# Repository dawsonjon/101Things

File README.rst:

.. image:: https://readthedocs.org/projects/chips-20/badge/?version=latest
    :target: https://readthedocs.org/projects/chips-20/badge/?version=latest

101 Things
==========

Welcome to *101 Things*, a collection of projects that celebrate creativity and
hands-on ingenuity.  If you share a passion for making things, you've come to
the right place. Each project uses simple designs, and basic tools, to push the
creative boundaries of a home tinkerer.  Join me on this exploration of
crafting, coding, and constructing, as we unlock the magic of making, one
project at a time.

Documentation
-------------

`ReadTheDocs <https://101-things.readthedocs.io/en/latest/>`_.

Projects so far
---------------

Pi Pico Rx - A crystal radio for the digital age?
"""""""""""""""""""""""""""""""""""""""""""""""""

.. image:: docs/images/thumbnail5.png
  :target: https://github.com/dawsonjon/PicoRX/assets/717535/4846c78d-21c3-42e8-bcdf-278cc2bdadcb

DIY Multi-Effect Guitar Unit
""""""""""""""""""""""""""""

.. image:: docs/images/headphone_amp.jpg
  :align: center

Raspberry Pi Pico Ham Radio Transmitter
"""""""""""""""""""""""""""""""""""""""

.. image::  docs/images/HamTransmitterThumbnail.png
  :target: https://youtu.be/PbhmQfPkNL0

Raspberry Pi Power and SWR Meter
"""""""""""""""""""""""""""""""""""""""

.. image::  docs/images/power_meter_thumbnail.png
  :target: https://youtu.be/_b22atCT8KU

Raspberry Pi Pico FM Radio
"""""""""""""""""""""""""""

.. image:: docs/images/fm_radio_thumbnail.png
  :target: https://youtu.be/bj8MgL6k2tU

8-inch Dobsonian Telescope
""""""""""""""""""""""""""

.. image::  docs/images/telescope_thumbnail.png
  :target: https://youtu.be/KxbAh8ndkbY

Breadboard Software Defined Radio
"""""""""""""""""""""""""""""""""

.. image::  docs/images/breadboard_radio_thumbnail.png
  :target: https://youtu.be/lS1ZRMIYLjA

SSTV Decoder
""""""""""""

.. image::  docs/images/sstv/thumbnail.png
  :target: https://youtu.be/FraeQk6Fj2I

Junkbox Arcade
""""""""""""""

.. image::  docs/images/junkbox_arcade/thumbnail.png
  :target: https://youtu.be/QSweNG6Ulxg

Hamfist CW Decoder
""""""""""""""""""

.. image::  docs/images/ham_fist/thumbnail.png
  :target: https://youtu.be/rBRf3QOt4wc

Getting the Code
----------------

.. code::

  sudo apt install git
  git clone https://github.com/dawsonjon/101Things.git

Install Pi Pico SDK
-------------------

Follow the `Getting started with the Raspberry Pi Pico <https://datasheets.raspberrypi.com/pico/getting-started-with-pico.pdf>`_ quick start guide to install the C/C++ SDK.

.. code::

  sudo apt install wget #if wget not installed
  wget https://raw.githubusercontent.com/raspberrypi/pico-setup/master/pico_setup.sh
  chmod +x pico_setup.sh
  ./pico_setup.sh

Build Projects
--------------

Some projects may target either the pico or pico_w variant, although those that use the wireless functionality can only be built on the pi-pico.

To build for pico_w:
""""""""""""""""""""

.. code::

  mkdir build
  cd build
  cmake -DPICO_BOARD=pico_w -DPICO_SDK_PATH=~/pico/pico-sdk ..
  make

To build for pico:
""""""""""""""""""

.. code::

  mkdir build
  cd build
  cmake -DPICO_BOARD=pico -DPICO_SDK_PATH=~/pico/pico-sdk ..
  make

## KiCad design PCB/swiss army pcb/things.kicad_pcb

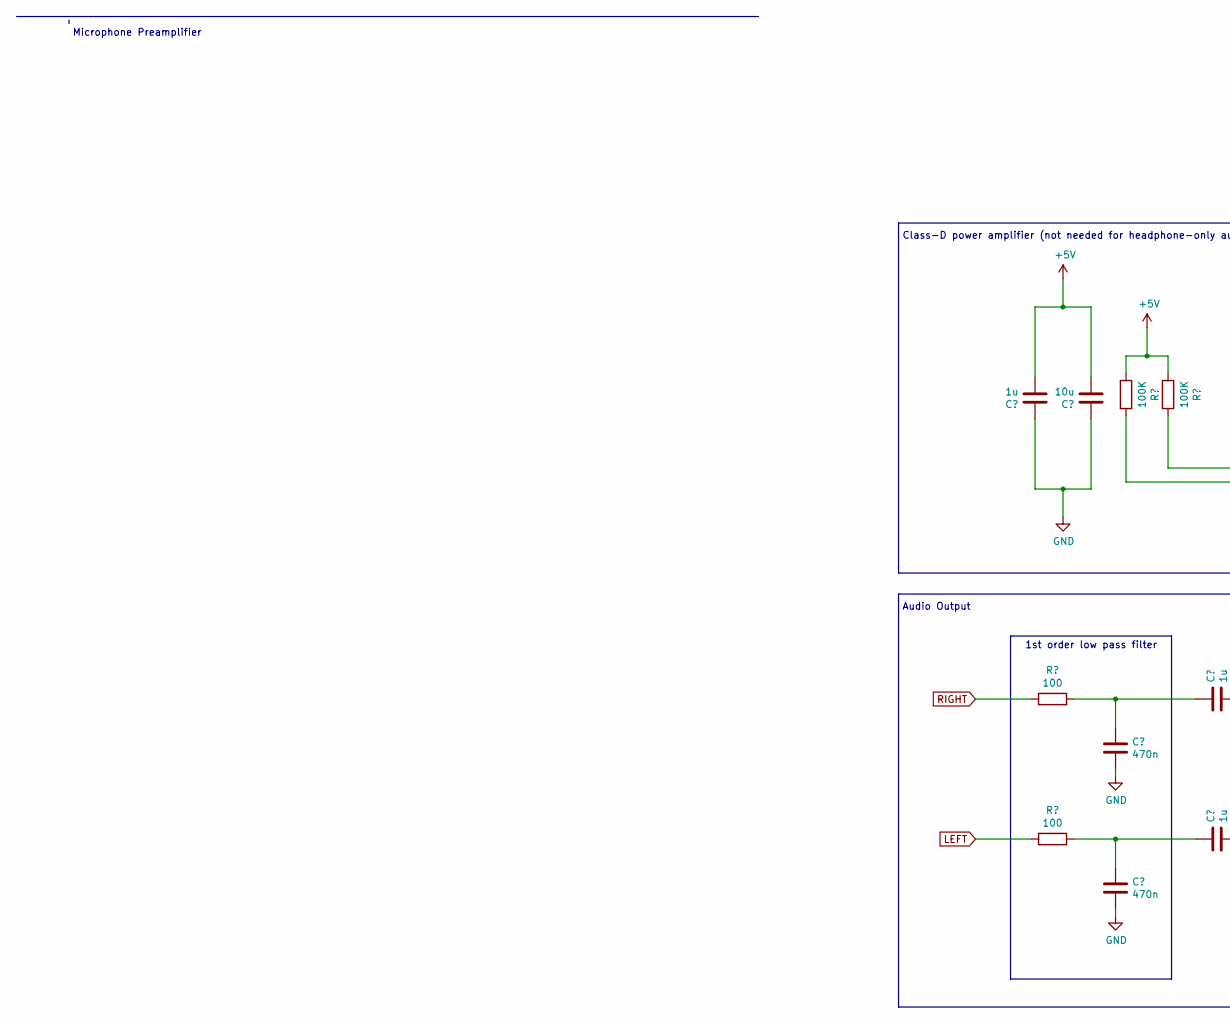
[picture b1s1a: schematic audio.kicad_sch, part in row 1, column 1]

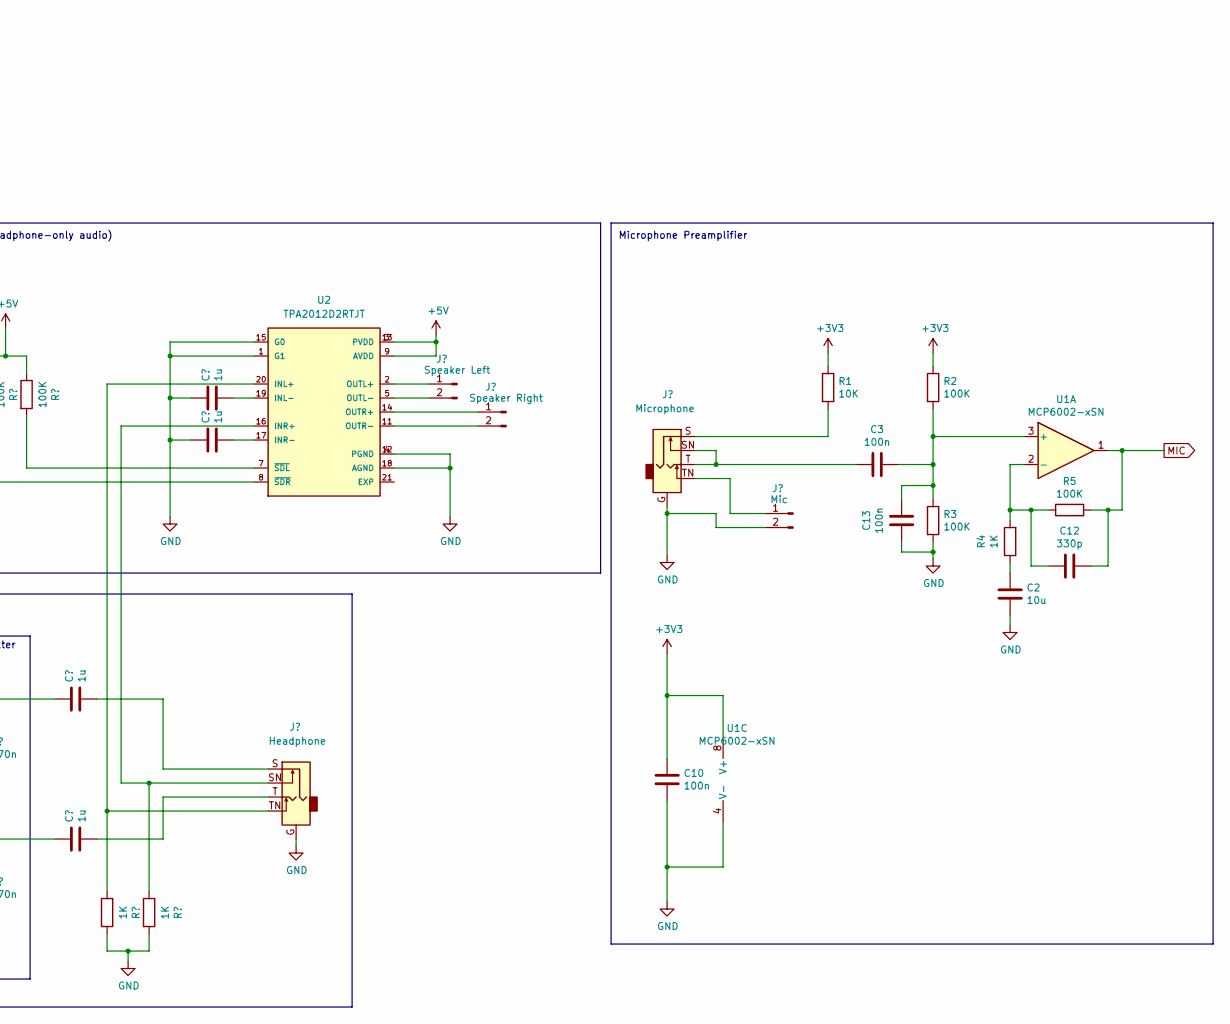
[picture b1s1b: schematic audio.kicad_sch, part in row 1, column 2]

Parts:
C1, C2: 10u; C_0805_2012Metric
C3, C10, C13: 100n; C_0805_2012Metric
C4, C5, C6, C9, C11: 1u; C_0805_2012Metric
C7, C8: 470n; C_0805_2012Metric
C12: 330p; C_0805_2012Metric
J1: Microphone; jack3.5mm switched
J2: Mic; PinHeader_1x02_P2.54mm_Vertical
J3: Headphone; jack3.5mm switched
J4: Speaker Left; PinHeader_1x02_P2.54mm_Vertical
J5: Speaker Right; PinHeader_1x02_P2.54mm_Vertical
R1: 10K; R_0805_2012Metric
R2, R3, R5, R8, R9: 100K; R_0805_2012Metric
R4, R10, R11: 1K; R_0805_2012Metric
R6, R7: 100; R_0805_2012Metric
U1: MCP6002-xSN; SOIC-8_3.9x4.9mm_P1.27mm
U2: TPA2012D2RTJT; QFN50P400X400X80-21N270X270; PARTREV NA; DigiKey_Part_Number 296-26878-2-ND

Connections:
+3V3: C10.1, R1.1, R2.1, U1.8 (V+); also elsewhere on the board
+5V: C1.2, C9.2, R8.1, R9.1, U2.3 (PVDD), U2.9 (AVDD), U2.13 (PVDD); also elsewhere on the board
GND: C1.1, C2.2, C4.1, C7.2, C8.2, C9.1, C10.2, C11.1, C13.1, J1.G, J2.2, J3.G, R3.2, R10.2, R11.2, U1.4 (V-), U2.1 (G1), U2.4 (PGND), U2.12 (PGND), U2.15 (G0), U2.18 (AGND); also elsewhere on the board
LEFT: R7.1; also elsewhere on the board
MIC: C12.2, R5.2, U1.1; also elsewhere on the board
unnamed: C2.1, R4.1
unnamed: C3.1, J1.SN, J1.T
unnamed: C5.1, C7.1, R6.2
unnamed: C5.2, J3.S
unnamed: C6.1, C8.1, R7.2
unnamed: C6.2, J3.T
unnamed: J1.S, R1.2
unnamed: J1.TN, J2.1
unnamed: J4.1, U2.2 (OUTL+)
unnamed: J4.2, U2.5 (OUTL-)
unnamed: J5.1, U2.14 (OUTR+)
unnamed: J5.2, U2.11 (OUTR-)
unnamed: C3.2, C13.2, R2.2, R3.1, U1.3 (+)
unnamed: C12.1, R4.2, R5.1, U1.2 (-)
unnamed: J3.TN, R10.1, U2.20 (INL+)
unnamed: C4.2, U2.19 (INL-)
unnamed: J3.SN, R11.1, U2.16 (INR+)
unnamed: C11.2, U2.17 (INR-)
unnamed: R8.2, U2.7 (~SDL)
unnamed: R9.2, U2.8 (~SDR)
RIGHT: R6.1; also elsewhere on the board

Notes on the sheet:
1st order low pass filter
Microphone Preamplifier
Audio Output
Class-D power amplifier (not needed for headphone-only audio)

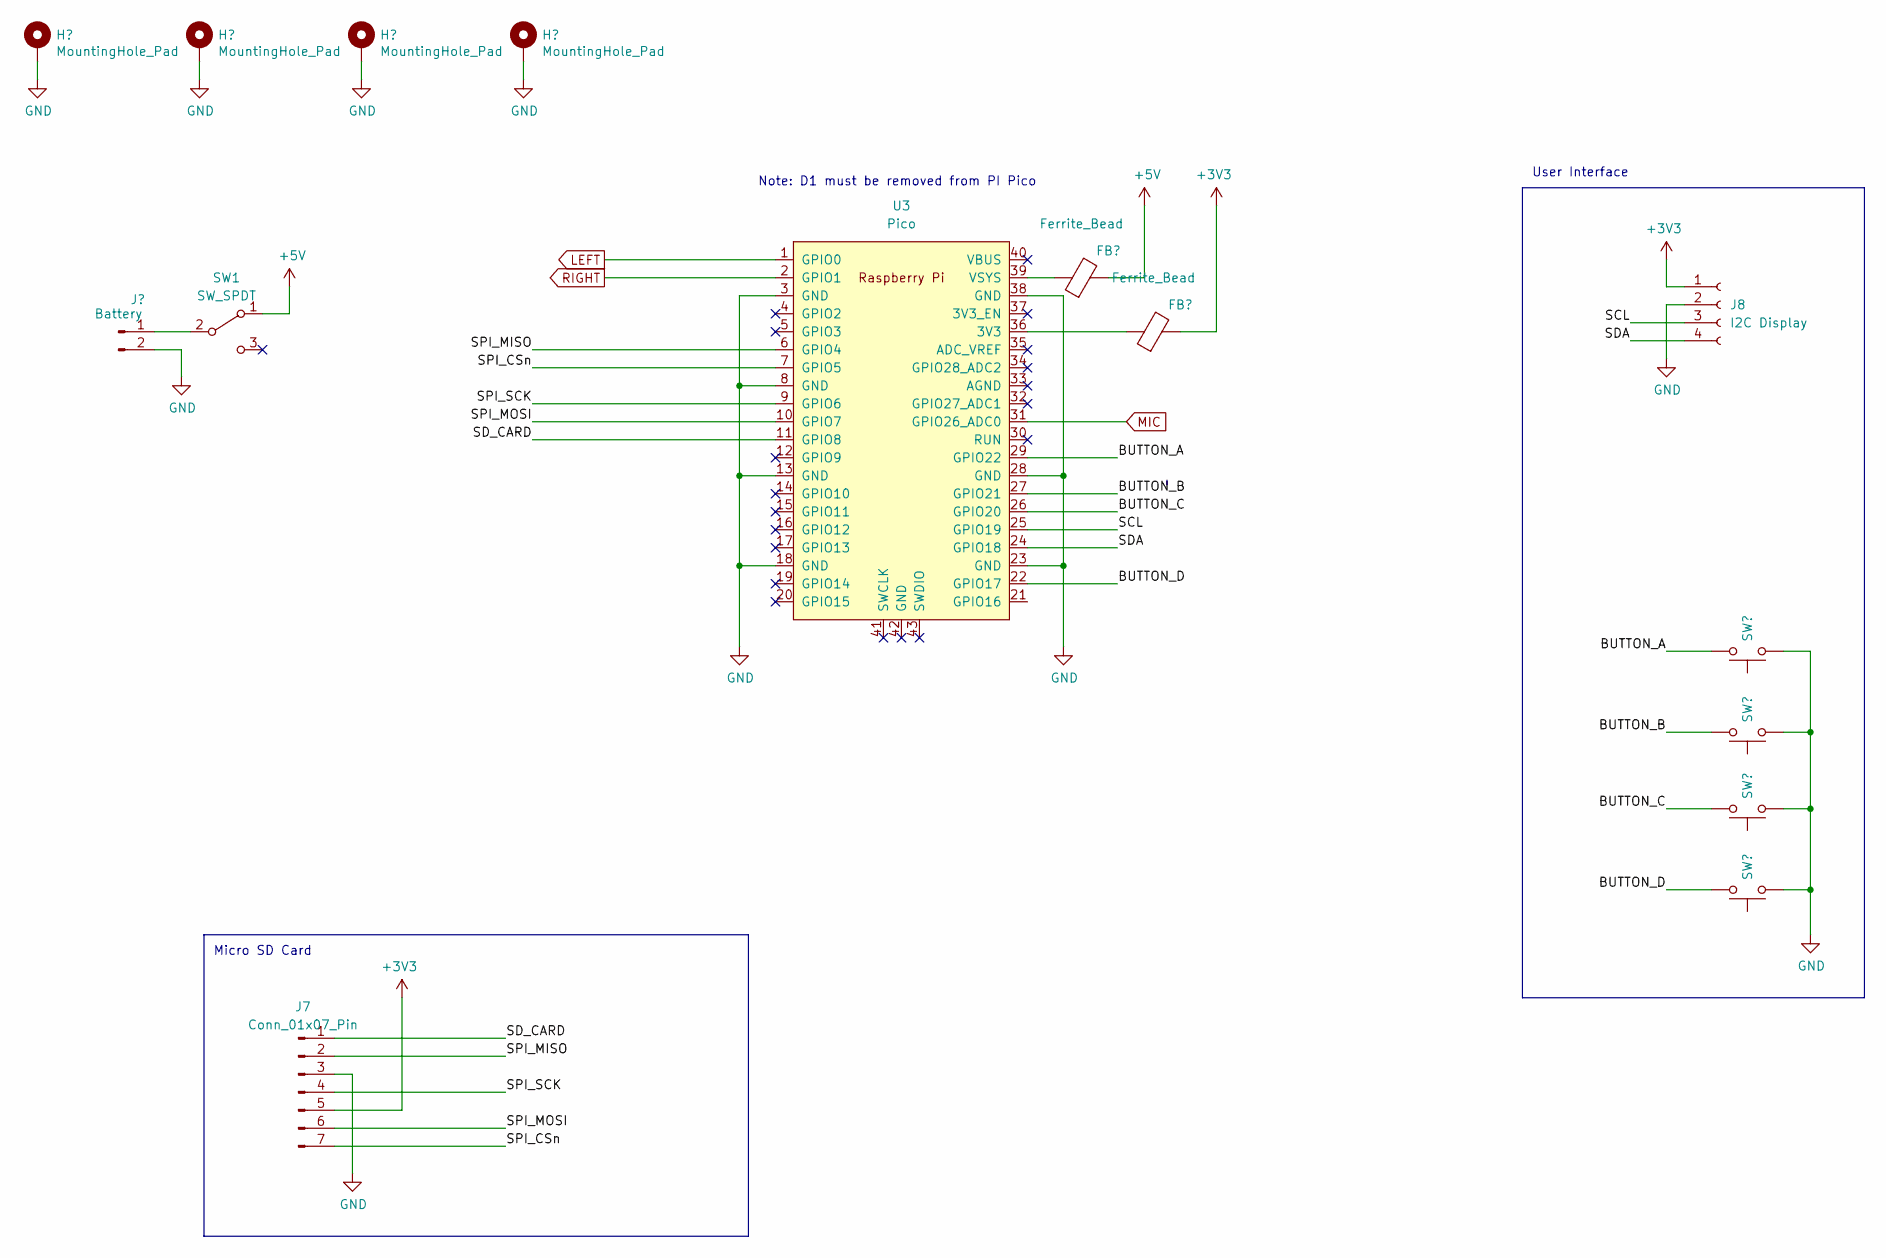
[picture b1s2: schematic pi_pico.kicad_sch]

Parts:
FB1, FB2: Ferrite_Bead; L_0805_2012Metric
H1, H2, H3, H4: MountingHole_Pad; MountingHole_3.2mm_M3_Pad
J6: Battery; PinHeader_1x02_P2.54mm_Vertical
J7: Conn_01x07_Pin; BOB-00544 MicroSD
J8: I2C Display; SDD1306
SW1: SW_SPDT; SW_Slide_1P2T_CK_OS102011MS2Q
SW2, SW3, SW4, SW5: SW_Push; SW_Tactile_Straight_KSA0Axx1LFTR
U3: Pico; RPi_Pico_SMD_TH

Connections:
+3V3: FB2.2, J7.5, J8.1; also elsewhere on the board
+5V: FB1.2, SW1.1 (A); also elsewhere on the board
/PI Pico/BUTTON_A: SW2.2, U3.29 (GPIO22)
/PI Pico/BUTTON_B: SW3.2, U3.27 (GPIO21)
/PI Pico/BUTTON_C: SW4.2, U3.26 (GPIO20)
/PI Pico/BUTTON_D: SW5.2, U3.22 (GPIO17)
/PI Pico/SCL: J8.3, U3.25 (GPIO19)
/PI Pico/SDA: J8.4, U3.24 (GPIO18)
/PI Pico/SD_CARD: J7.1, U3.11 (GPIO8)
/PI Pico/SPI_CSn: J7.7, U3.7 (GPIO5)
/PI Pico/SPI_MISO: J7.2, U3.6 (GPIO4)
/PI Pico/SPI_MOSI: J7.6, U3.10 (GPIO7)
/PI Pico/SPI_SCK: J7.4, U3.9 (GPIO6)
GND: H1.1, H2.1, H3.1, H4.1, J6.2, J7.3, J8.2, SW2.1, SW3.1, SW4.1, SW5.1, U3.3 (GND), U3.8 (GND), U3.13 (GND), U3.18 (GND), U3.23 (GND), U3.28 (GND), U3.38 (GND); also elsewhere on the board
LEFT: U3.1 (GPIO0); also elsewhere on the board
MIC: U3.31 (GPIO26_ADC0); also elsewhere on the board
unnamed: J6.1, SW1.2 (B)
unnamed: FB2.1, U3.36 (3V3)
unnamed: FB1.1, U3.39 (VSYS)
RIGHT: U3.2 (GPIO1); also elsewhere on the board

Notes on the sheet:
Micro SD Card
Note: D1 must be removed from PI Pico
User Interface

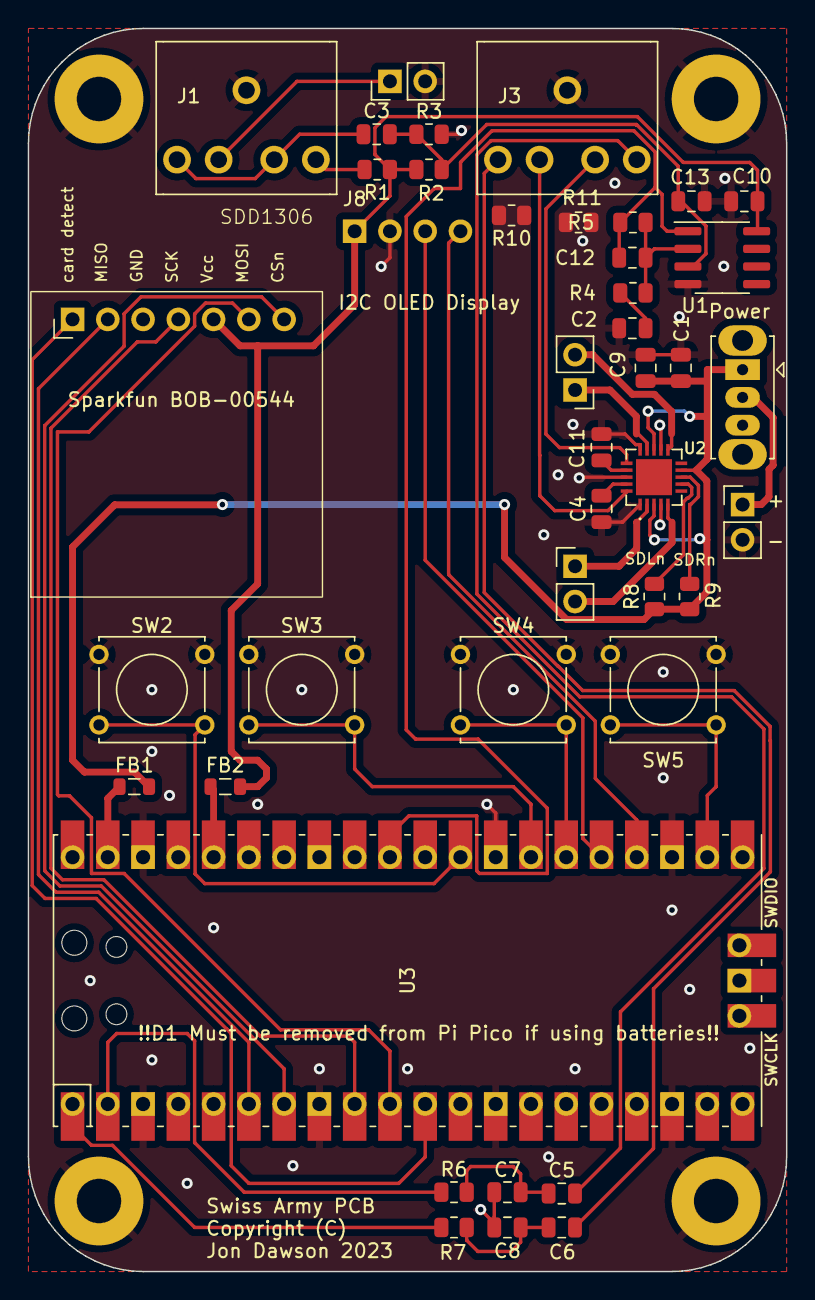
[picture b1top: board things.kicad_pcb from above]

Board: 2 copper layers, 54.6 x 89.5 mm, 46 parts (0 on the bottom side), 40 nets.

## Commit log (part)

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2023-09-29 Get TCPServer and audio working
2023-09-30 tidy up
2023-10-01 Tidy up code
2023-10-01 Get duplex audio streaming working
2023-10-01 Add dalek voice changer
2023-10-01 Add readthedocs.yaml
2023-10-01 Add sphinx documentation
2023-10-01 Add README.rst
2023-10-01 Add .gitignore
2023-10-04 Add USB/Flash wifi connection method
2023-10-06 Add ability to connect as client and server
2023-10-24 Guitar Effects
2023-10-29 Basic Timer Working
2023-11-02 Add menu to guitar effects
2023-11-05 Move PSU setting to its own library
2023-11-11 Add FFT based EQ
2023-11-14 start converting to fixed point
2023-11-14 convert to fixed
2023-11-19 Use fixed point implementation of effects
2023-11-19 Add reverb effect
2023-11-25 Add patches to guitar effect
2023-11-26 Get patches working
2023-11-30 Add Schematic PDF
2023-11-30 Add uf2 file
2023-12-03 Draft documentation for guitar effects
2023-12-07 Update Diagrams
2023-12-07 Add documentation for radio
2023-12-09 Add Ring Tones to timer
2023-12-09 Add timer documentation
2023-12-12 frequency generator experiments
2023-12-13 DMA based frequency generator working
2023-12-15 Attempt at DMA based phase correction
2023-12-18 Add inverted magnitude
2023-12-19 Add Microphone
2023-12-21 Fix issue with NCO
2023-12-21 Add headers
2023-12-21 Add license file
2023-12-21 code tidy
2023-12-23 Get SSB working
2023-12-30 Update transmitter test plots
2023-12-31 Update Documents
2024-01-24 Add amplifier experiments to transmitter
2024-01-24 Fix documentation
2024-01-26 Fix build issue when targetting pi-pico w. Update build instructions to reflect that projects can be built for either pico or pico_w
2024-01-26 Set RF level to 0 when serial link drops
2024-01-28 tidy up transmit python script and transmitter.cpp example
2024-01-28 Update image
2024-02-01 Add some details desribing transistor selection
2024-02-03 Add missing include
2024-02-04 Fix issues with unreliable streaming
2024-02-04 Update headers for python files
2024-02-05 Add fm radio example
2024-02-05 Update breadboard/serial example
2024-02-10 Add schemetic for FM radio
2024-02-12 Make seperate build targets for mixer and polar amplifier, and seperate examples using microphone and serial streaming
2024-02-12 Point to latest PicoRx repo
2024-02-14 Write some documentation for the RF power meter
2024-02-14 reduce contents depth
2024-02-15 Add link to video
2024-02-18 Add design for mirror cell
2024-03-16 Fix battery level indicator
2024-03-26 Update docs for FM radio
2024-04-01 Add links to video
2024-04-01 Correct image link
2024-04-01 Add link to software
2024-04-13 Implement Inclinometer firmware in C++
2024-04-29 Add design files for telescope
2024-05-06 Update for part 1
2024-05-06 fix picture
2024-05-27 Update documentation for telescope part 2
2024-06-29 Add setup menu to inclinometer
2024-06-29 Remove startup delay
2024-07-09 Modify scaling in modulator
2024-07-09 update modulator scaling
2024-07-09 clamp mic input
2024-07-10 Get frequency generator working
2024-07-10 Add a simple test tone generator
2024-07-10 Remove incorrect clamping code
2024-07-14 Switch to building in Arduino
2024-07-14 Update transmitter to use clock speed specified by Arduino
2024-07-14 Add documentation for inclinometer
2024-07-14 Add paragraph about PSU
2024-07-24 Add walkie-talkie sketch
2024-07-28 Get Walkie Talkie Working
2024-07-31 Fix issue where band and spacing get overwritten in set_frequency
2024-08-11 Update documents for breadboard radio
2024-08-11 Fix error in schematic
2024-08-25 Update documentation
2024-10-10 Add parts list
2024-11-21 update docs
2024-12-12 First go at SSTV decoder
2024-12-14 Complete Arduino Sketch and test on hardware
2024-12-15 Tweaks to TFT
2025-01-03 Make sstv decoder a submodule
2025-01-03 Add documentation for SSTV decoder
2025-01-03 Update submodule
2025-01-05 Update to latest SSTV decoder
2025-05-16 Add planetarium as submodule
2025-05-16 update submodules
2025-05-16 Add documentation for planetarium
2025-05-16 Update planetarium docs
2025-05-22 Use latest version of planetarium
2025-07-21 Add link to github page
2025-08-26 Add documentation for breadboard radio part 4
2025-10-07 Update SSTV docs
2025-11-19 Add documentation for JunkboxArcade
2025-11-19 Add junkbox arcade
2025-11-22 Update docs to reference video
2025-11-25 Fix typos
2025-11-29 Point to latest version of JunkboxArcade repo
2026-01-11 Update documents for HamFist
2026-01-20 Shrink images
2026-01-26 Convert to I2S amplifier
2026-01-30 Add a pseudo P2P mode so that walkie talkies work without wifi
2026-01-30 Convert to UDP Streaming, move I2S outputs to more convenient pins
2026-02-01 Add link to latest
2026-02-01 Add mermaid extension to requirements
2026-02-01 Fix display wiring table
2026-02-01 Start documenting walkie-talkies
2026-02-08 Add docs for walkie-talkie
2026-02-08 Add images to docs
2026-02-27 Update Walkie-Talkie Docs
2026-02-28 Add youtube link to docs
2026-03-01 Add link

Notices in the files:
PCB/swiss army pcb/things.kicad_pcb:
Copyright (C)
